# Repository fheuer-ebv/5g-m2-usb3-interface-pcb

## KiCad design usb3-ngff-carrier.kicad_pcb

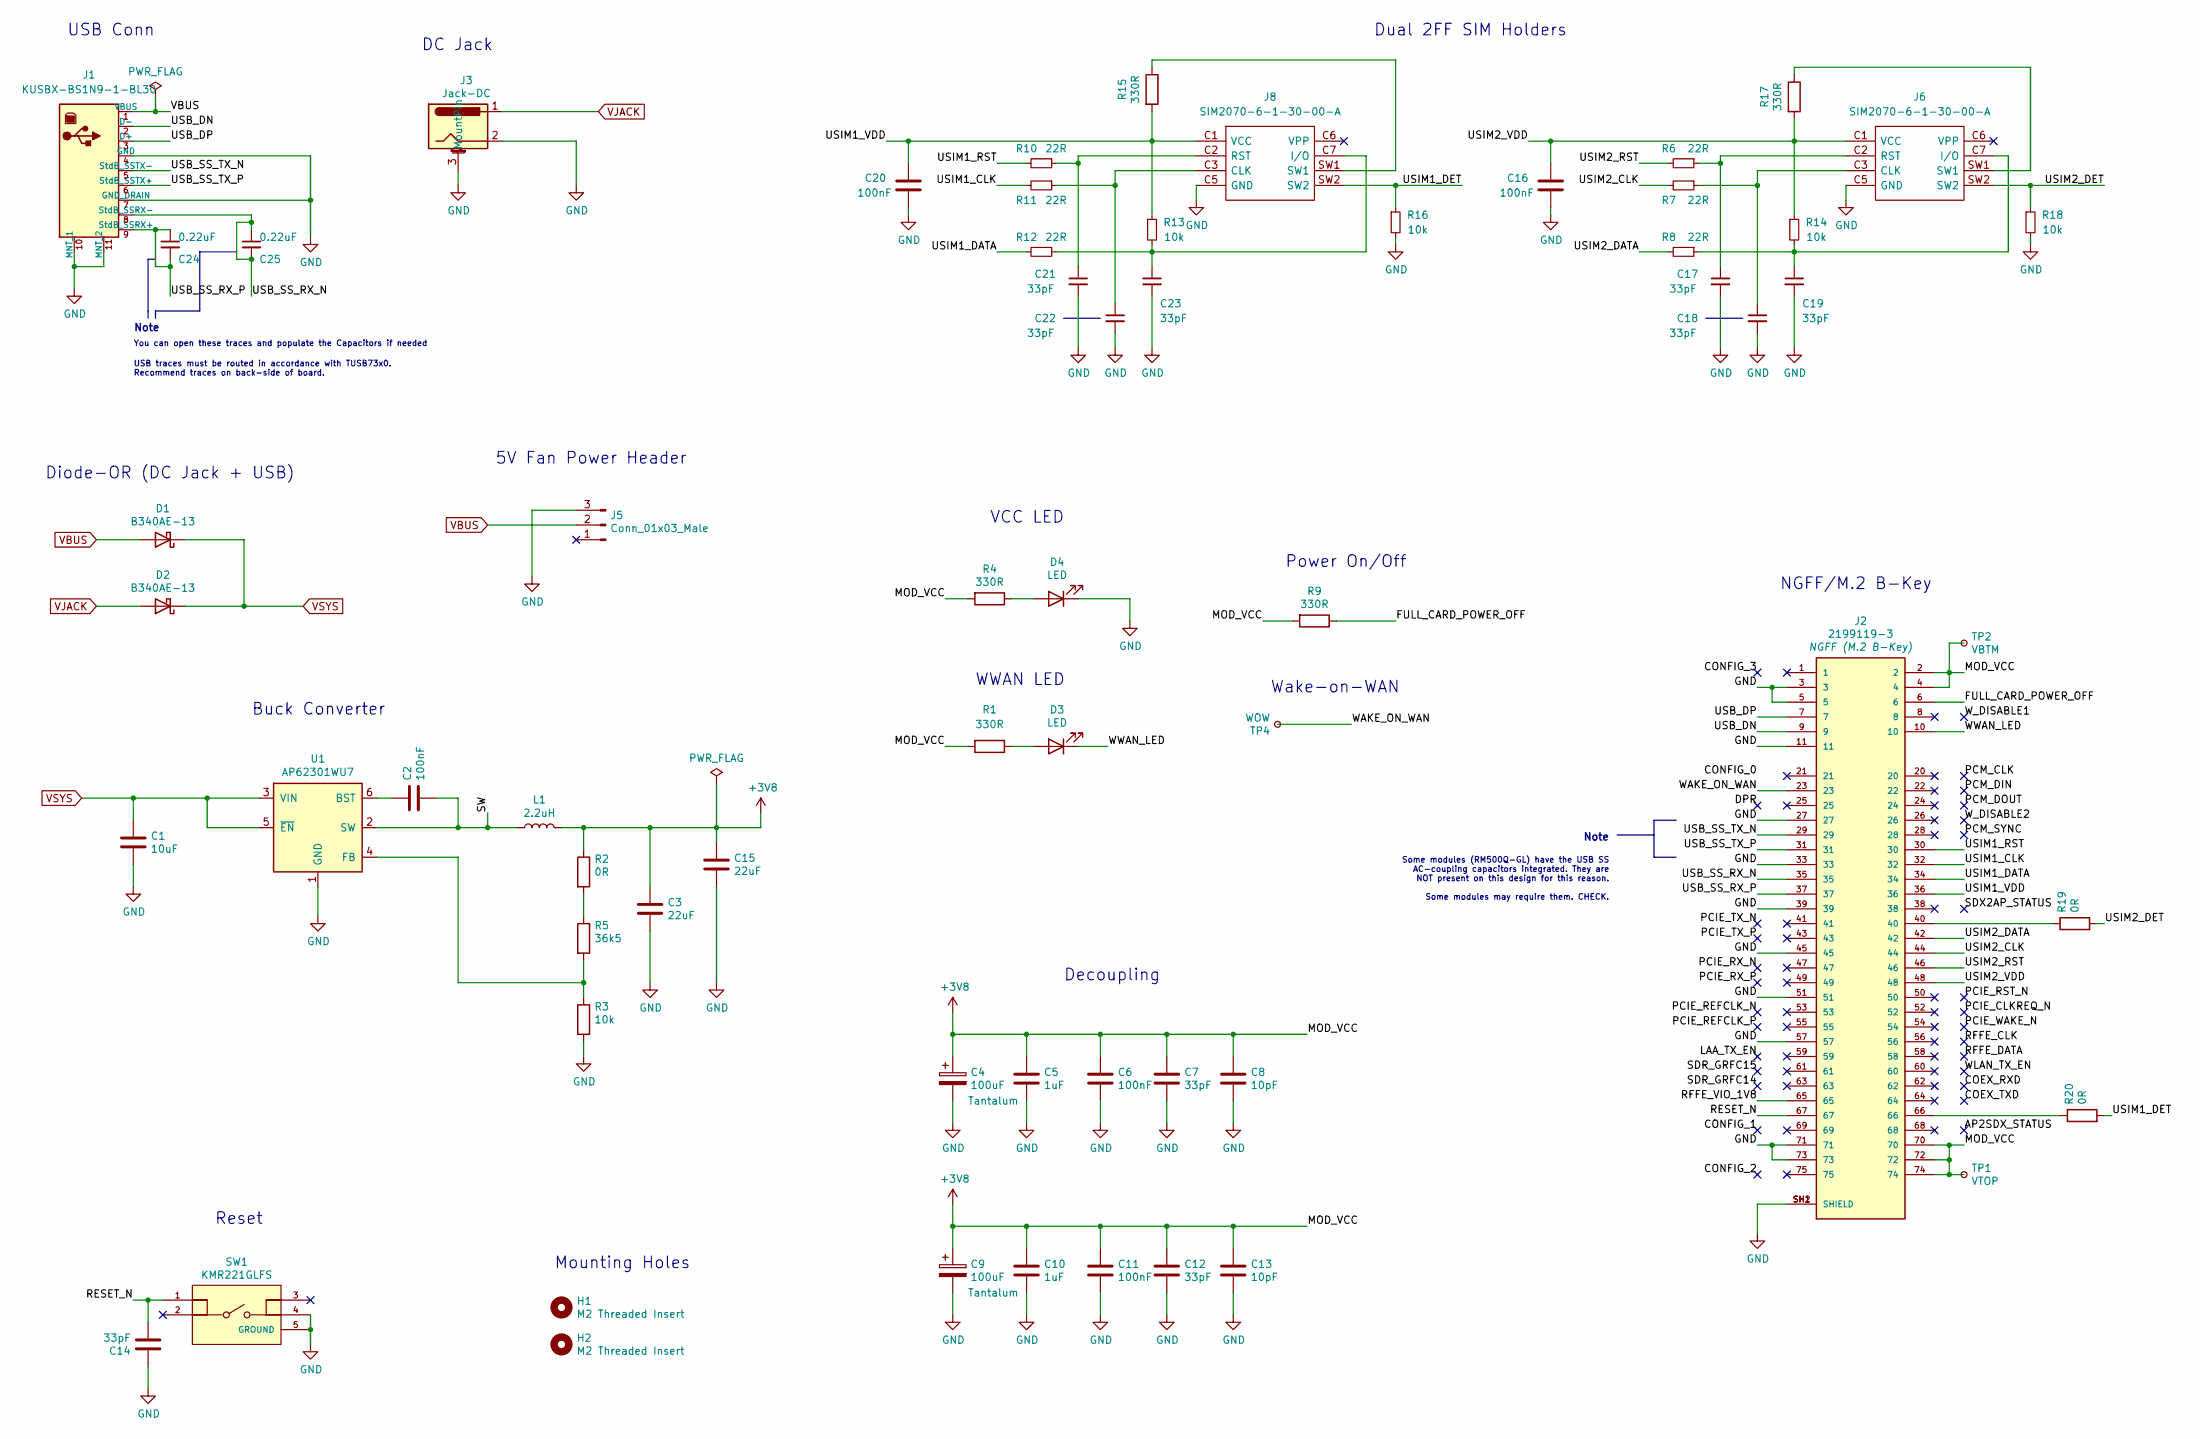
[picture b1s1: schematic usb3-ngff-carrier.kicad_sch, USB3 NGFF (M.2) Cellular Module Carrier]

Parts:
C1: 10uF; C_0805_2012Metric; MPN GRM21BR71A106KA73K
C2, C6, C11, C16, C20: 100nF; C_0603_1608Metric; MPN C0603C104K3RAC
C3, C15: 22uF; C_1210_3225Metric; MPN CL32B226MOJNNNE
C4, C9: 100uF; CP_EIA-3528-21_Kemet-B; MPN TCJB107M006R0040
C5, C10: 1uF; C_0603_1608Metric; MPN CGA3E1X7R1C105K080AC
C7, C12, C14, C17, C18, C19, C21, C22, C23: 33pF; C_0603_1608Metric; MPN 06035A330KAT2A
C8, C13: 10pF; C_0603_1608Metric; MPN 06035A100JAT4A
C24, C25: 0.22uF; C_0402_1005Metric_Pad0.74x0.62mm_HandSolder; MPN CGA2B3X7R1E224K050BB
D1, D2: B340AE-13; D_SMA; MPN B340AE-13
D3, D4: LED; LED_0805_2012Metric; MPN APTD2012LQBC/D
H1, H2: M2 Threaded Insert; 9774015243RStandoff; MPN 9774020243R
J1: KUSBX-BS1N9-1-BL30; Wurth-692221030100-0-0-MFG; MPN KUSBX-BS1N9-1-BL30
J2: 2199119-3; TE_2199119-3; MPN 2199119-3
J3: Jack-DC; BarrelJack_Wuerth_6941xx301002; MPN 694106301002
J5: Conn_01x03_Male; PinHeader_1x03_P2.54mm_Vertical
J6: SIM2070-6-1-30-00-A; SIM2070613000A_card; MPN 640-SIM2070613000A
J8: SIM2070-6-1-30-00-A; SIM2070613000A_card; Mouser Part Number 640-SIM2070613000A
L1: 2.2uH; L_Coilcraft_XAL5030; MPN XAL5030-222MEC
R1, R4, R9, R15, R17: 330R; R_0603_1608Metric; MPN CRCW0603330RFKEAC
R2, R19, R20: 0R; R_0603_1608Metric; MPN RC0603FR-070RL
R3, R13, R14, R16, R18: 10k; R_0603_1608Metric; MPN CR0603-FX-1002ELF
R5: 36k5; R_0603_1608Metric; MPN CRCW060336K5FKEAC
R6, R7, R8, R10, R11: 22R; R_0603_1608Metric; MPN CRCW060322R0JNEAC
R12: 22R; R_0603_1608Metric
SW1: KMR221GLFS; CK-KMR221GLFS-MFG; MPN KMR221GLFS
TP1: VTOP; TestPoint_Pad_D1.5mm
TP2: VBTM; TestPoint_Pad_D1.5mm
TP4: WOW; TestPoint_Pad_D1.5mm
U1: AP62301WU7; TSOT-23-6; MPN AP62301WU-7

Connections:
+3V8: C3.1, C4.1, C5.1, C6.1, C7.1, C8.1, C9.1, C10.1, C11.1, C12.1, C13.1, C15.1, J2.2, J2.4, J2.70, J2.72, J2.74, L1.2, R1.2, R2.1, R4.2, R9.2, TP1.1, TP2.1
/FULL_CARD_POWER_OFF: J2.6, R9.1
/RESET_N: C14.2, J2.67, SW1.1
/RFFE_VIO_1V8: J2.65
/SW: C2.2, L1.1, U1.2 (SW)
/USB_DN: J1.2 (D-), J2.9
/USB_DP: J1.3 (D+), J2.7
/USB_SS_RX_N: C25.1, C25.2, J1.8 (StdB_SSRX-), J2.35
/USB_SS_RX_P: C24.1, C24.2, J1.9 (StdB_SSRX+), J2.37
/USB_SS_TX_N: J1.5 (StdB_SSTX-), J2.29
/USB_SS_TX_P: J1.6 (StdB_SSTX+), J2.31
/USIM1_CLK: J2.32, R11.2
/USIM1_DATA: J2.34, R12.2
/USIM1_DET: J8.SW2, R16.1, R20.2
/USIM1_RST: J2.30, R10.2
/USIM1_VDD: C20.1, J2.36, J8.C1 (VCC), R13.1, R15.2
/USIM2_CLK: J2.44, R7.2
/USIM2_DATA: J2.42, R8.2
/USIM2_DET: J6.SW2, R18.1, R19.2
/USIM2_RST: J2.46, R6.2
/USIM2_VDD: C16.1, J2.48, J6.C1 (VCC), R14.1, R17.2
/WAKE_ON_WAN: J2.23, TP4.1
/WWAN_LED: D3.1 (K), J2.10
GND: C1.2, C3.2, C4.2, C5.2, C6.2, C7.2, C8.2, C9.2, C10.2, C11.2, C12.2, C13.2, C14.1, C15.2, C16.2, C17.2, C18.2, C19.2, C20.2, C21.2, C22.2, C23.2, D4.1 (K), J1.4 (GND), J1.7 (GND_DRAIN), J1.10 (MNT_1), J1.11 (MNT_2), J2.3, J2.5, J2.11, J2.27, J2.33, J2.39, J2.45, J2.51, J2.57, J2.71, J2.73, J2.SH1 (SHIELD), J2.SH2 (SHIELD), J3.2, J3.3 (MountPin), J5.3, J6.C5 (GND), J8.C5 (GND), R3.2, R16.2, R18.2, SW1.4, SW1.5 (GROUND), U1.1 (GND)
unnamed: C2.1, U1.6 (BST)
unnamed: C17.1, J6.C2 (RST), R6.1
unnamed: C18.1, J6.C3 (CLK), R7.1
unnamed: C19.1, J6.C7 (I/O), R8.1, R14.2
unnamed: C21.1, J8.C2 (RST), R10.1
unnamed: C22.1, J8.C3 (CLK), R11.1
unnamed: C23.1, J8.C7 (I/O), R12.1, R13.2
unnamed: D3.2 (A), R1.1
unnamed: D4.2 (A), R4.1
unnamed: J2.40, R19.1
unnamed: J2.66, R20.1
unnamed: J6.SW1, R17.1
unnamed: J8.SW1, R15.1
unnamed: R2.2, R5.1
unnamed: R3.1, R5.2, U1.4 (FB)
VBUS: D1.2 (A), J1.1 (VBUS), J5.2
VJACK: D2.2 (A), J3.1
VSYS: C1.1, D1.1 (K), D2.1 (K), U1.3 (VIN), U1.5 (~EN)

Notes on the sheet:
Wake-on-WAN
USB Conn
5V Fan Power Header
VCC LED
USB traces must be routed in accordance with TUSB73x0. Recommend traces on back-side of board.
Buck Converter
You can open these traces and populate the Capacitors if needed
Note
Some modules (RM500Q-GL) have the USB SS AC-coupling capacitors integrated. They are NOT present on this design for this reason. Some modules may require them. CHECK.
Power On/Off
Decoupling
WWAN LED
Diode-OR (DC Jack + USB)
Mounting Holes
NGFF/M.2 B-Key
Reset
DC Jack
Dual 2FF SIM Holders

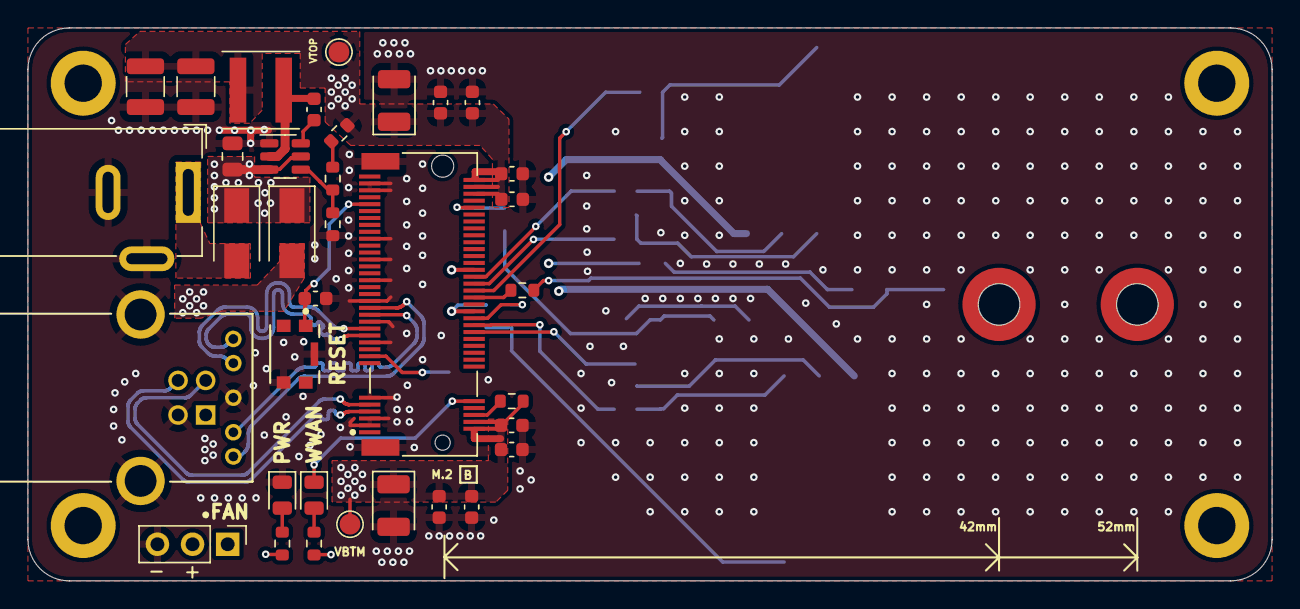
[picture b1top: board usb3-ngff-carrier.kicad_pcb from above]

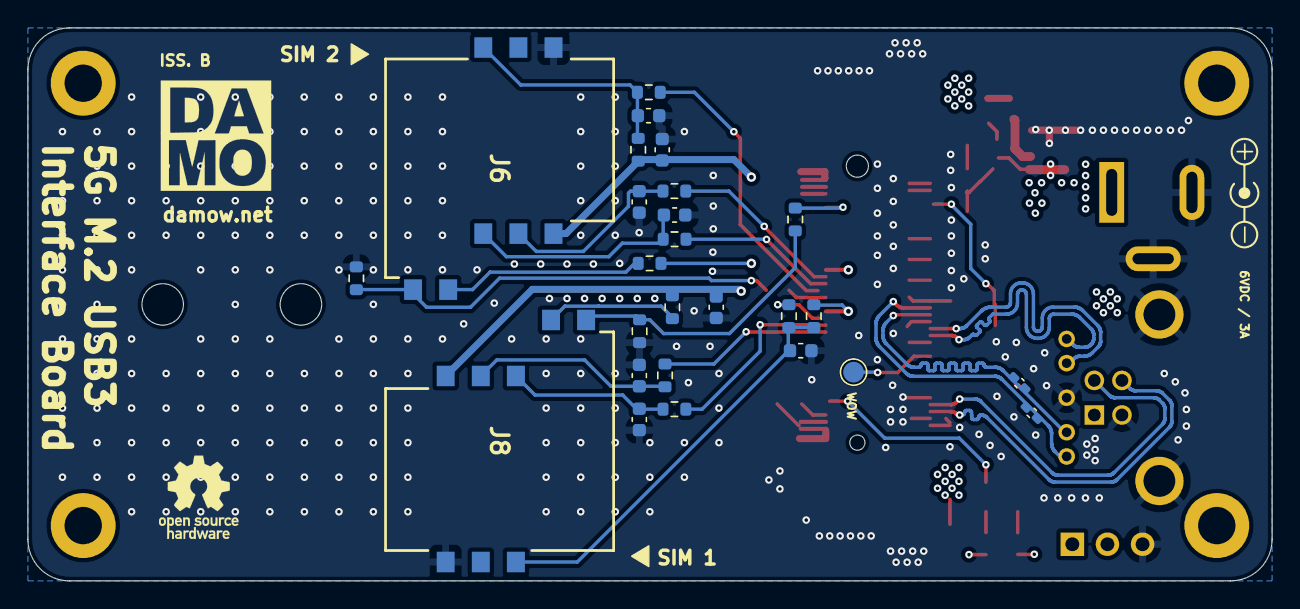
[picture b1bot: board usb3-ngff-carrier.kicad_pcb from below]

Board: 4 copper layers, 90.0 x 40.0 mm, 63 parts (26 on the bottom side), 41 nets.

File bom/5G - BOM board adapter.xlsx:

Reference | Quantity | Value | Footprint | MPN | Mfr
C1 | 1.0 | 10uF | Capacitor_SMD:C_0805_2012Metric | GRM21BR71A106KA73K | MuRata Electronics
C2 C6 C11 C16 C20 | 5.0 | 100nF | Capacitor_SMD:C_0603_1608Metric | C0603C104K3RAC | KEMET
C24 C25 | 2.0 | 0.22uF | Capacitor_SMD:C_0402_1005Metric_Pad0.74x0.62mm_HandSolder | CGA2B3X7R1E224K050BB | TDX
C3 C15 | 2.0 | 22uF | Capacitor_SMD:C_1210_3225Metric | CL32B226MOJNNNE | Samsung Electro-Mechanics
C4 C9 | 2.0 | 100uF | Capacitor_Tantalum_SMD:CP_EIA-3528-21_Kemet-B | TCJB107M006R0040 | AVX
C5 C10 | 2.0 | 1uF | Capacitor_SMD:C_0603_1608Metric | CGA3E1X7R1C105K080AC | TDK
C7 C12 C14 C17 C18 C19 C21 C22 C23 | 9.0 | 33pF | Capacitor_SMD:C_0603_1608Metric | 06035A330KAT2A | AVX
C8 C13 | 2.0 | 10pF | Capacitor_SMD:C_0603_1608Metric | 06035A100JAT4A | AVX
D1 D2 | 2.0 | MBRA340 | Diode_SMD:D_SMA | B340AE-13 | ON Semiconductor
D3 D4 | 2.0 | LED | LED_SMD:LED_0805_2012Metric | APTD2012LQBC/D | Kingbright
H1 H2 | 2.0 | M2 Threaded Insert | footprint:9774015243RStandoff | 9774020243R | Wurth
J1 | 1.0 | KUSBX-BS1N9-1-BL30 | footprint:Wurth-692221030100-0-0-MFG | KUSBX-BS1N9-1-BL30 | Kycon
J2 | 1.0 | 2199119-3 | footprint:TE_2199119-3 | 2199119-3 | TE Connectivity
J3 | 1.0 | Jack-DC | Connector_BarrelJack:BarrelJack_Wuerth_6941xx301002 | 694106301002 | Wurth
J6 J8 | 2.0 | SIM2070-6-1-30-00-A | SamacSys_Parts:SIM2070613000A_card | 640-SIM2070613000A | GCT (GLOBAL CONNECTOR TECHNOLOGY)
L1 | 1.0 | 2.2uH | Inductor_SMD:L_Coilcraft_XAL5030 | XAL5030-222MEC | Coilcraft
R1 R4 R9 R15 R17 | 5.0 | 330R | Resistor_SMD:R_0603_1608Metric | CRCW0603330RFKEAC
R2 R19 R20 | 3.0 | 0R | Resistor_SMD:R_0603_1608Metric | RC0603FR-070RL
R3 R13 R14 R16 R18 | 5.0 | 10k | Resistor_SMD:R_0603_1608Metric | CR0603-FX-1002ELF
R5 | 1.0 | 36k5 | Resistor_SMD:R_0603_1608Metric | CRCW060336K5FKEAC
R6 R7 R8 R10 R11 R12 | 6.0 | 22R | Resistor_SMD:R_0603_1608Metric | CRCW060322R0JNEAC
SW1 | 1.0 | KMR221GLFS | footprint:CK-KMR221GLFS-MFG | KMR221GLFS | C&K
U1 | 1.0 | AP62301WU7 | Package_TO_SOT_SMD:TSOT-23-6 | AP62301WU-7 | Diodes Inc.
J5 | 1.0 | Conn_01x03_Male | Connector_PinHeader_2.54mm:PinHeader_1x03_P2.54mm_Vertical

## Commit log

2022-06-07 feat: changes sim card holder to 2FF and adds missing PN to resistors
2022-06-08 feat: uses sim card detect pin
2022-06-08 feat: properly adds sim card detection
2022-06-08 feat: adds USB 2 capacitors pads for eventual assembly
2022-06-09 chore: moves M2 lenght silkscreen to the front
2022-06-09 fix: reduces optional USB Caps pads to 0402 and exposes a piece of their track
